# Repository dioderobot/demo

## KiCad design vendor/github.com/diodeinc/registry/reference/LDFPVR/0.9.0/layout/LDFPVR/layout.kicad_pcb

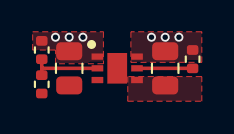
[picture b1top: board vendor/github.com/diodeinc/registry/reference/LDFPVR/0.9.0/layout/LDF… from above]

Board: 2 copper layers, 6 parts (0 on the bottom side), 5 nets.

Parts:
C1, C2: GRM21BZ71E106KE15K; C_0805_2012Metric
R1: ERJ-2RKF1003X; R_0402_1005Metric
R2: ERJ-2RKF2002X; R_0402_1005Metric
R3: ERJ-2RKF6192X; R_0402_1005Metric
U1: LDFPVR; SON65P200X200X100-7N-D

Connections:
ADJ: R2.1, R3.2, U1.2
GND: C1.2, C2.2, R2.2, U1.4, U1.7
VIN: C1.1, R1.1, U1.6
VOUT: C2.1, R3.1, U1.1
_EN: R1.2, U1.5

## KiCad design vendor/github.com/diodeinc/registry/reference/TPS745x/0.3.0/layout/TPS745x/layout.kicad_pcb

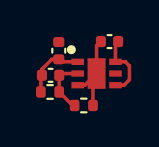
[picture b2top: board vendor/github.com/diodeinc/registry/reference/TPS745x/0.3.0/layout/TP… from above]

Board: 2 copper layers, 6 parts (0 on the bottom side), 4 nets.

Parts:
C1: GRM1555CYA103GE01D; C_0402_1005Metric
C2, C3: GRM155Z71A225KE44D; C_0402_1005Metric
IC1: TPS74501PCQWDRVRQ1
R1: ERJ-2RKF5602X; R_0402_1005Metric
R2: ERJ-2RKF1273X; R_0402_1005Metric

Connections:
GND: C2.2, C3.2, IC1.3, IC1.7, R1.2
VIN: C2.1, IC1.4, IC1.6
VOUT: C1.2, C3.1, IC1.1, R2.1
_FB: C1.1, IC1.2, R1.1, R2.2
